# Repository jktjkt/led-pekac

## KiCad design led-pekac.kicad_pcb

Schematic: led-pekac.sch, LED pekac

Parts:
C1, C2: 10uF/50V; C_1206_3216Metric_Pad1.33x1.80mm_HandSolder
C3, C4: 22uF/10V; C_1206_3216Metric_Pad1.33x1.80mm_HandSolder
C5, C7: 1uF; C_1206_3216Metric_Pad1.33x1.80mm_HandSolder
C6: 47nF; C_1206_3216Metric_Pad1.33x1.80mm_HandSolder
C8, C9: 100nF; C_1206_3216Metric_Pad1.33x1.80mm_HandSolder
C10: 100nF; C_1210_3225Metric_Pad1.33x2.70mm_HandSolder
C11: 10uF Tantalum; CP_EIA-3528-21_Kemet-B_Pad1.50x2.35mm_HandSolder
D1: LED1; LED_1206_3216Metric_Castellated
D2: LED2; LED_1206_3216Metric_Castellated
D3: PWR; LED_1206_3216Metric_Castellated
J1: Conn_01x04; PinHeader_1x04_P2.54mm_Horizontal
J2: 24V; CUI_TB002-500-04BE
J3: Console; PinHeader_1x03_P2.54mm_Vertical
J4: Pi Zero; Raspberry_Pi_Zero_Socketed_THT_FaceDown_MountingHoles
J5: Cool; CUI_TB002-500-04BE
J6: Warm; CUI_TB002-500-04BE
J7: Conn_01x40_Female; SAMTEC_HLE-120-02-X-DV-PE-BE_no_internal_holes_reversed
Q1, Q2: 2N7002; SOT-23
Q3, Q4: IPD50N06S4L08ATMA2; TO-252-2
R1: 47k; R_1206_3216Metric_Pad1.30x1.75mm_HandSolder
R2, R3, R4, R5: 220k; R_1206_3216Metric_Pad1.30x1.75mm_HandSolder
R6, R7, R8: 160; R_1206_3216Metric_Pad1.30x1.75mm_HandSolder
R9, R10, R11, R12: 12.1k 0.1%; R_1206_3216Metric_Pad1.30x1.75mm_HandSolder
SW1: Wheel; Bourns-PEC12R-3220F-S0024-MFG
TP1: 5V; TestPoint_Loop_D3.50mm_Drill1.4mm_Beaded
TP2: 3.3V (Pi); TestPoint_Loop_D3.50mm_Drill1.4mm_Beaded
TP3: 3.3VA (LED); TestPoint_Loop_D3.50mm_Drill1.4mm_Beaded
TP4: SDA; TestPoint_Loop_D3.50mm_Drill1.4mm_Beaded
TP5: SCL; TestPoint_Loop_D3.50mm_Drill1.4mm_Beaded
TP6: GND; TestPoint_Loop_D3.50mm_Drill1.4mm_Beaded
TP7: PWM0; TestPoint_Loop_D3.50mm_Drill1.4mm_Beaded
TP8: PWM1; TestPoint_Loop_D3.50mm_Drill1.4mm_Beaded
U1: SWITCHING-3TERM-5V; CONV_P78E05-1000
U2: SWITCHING-3TERM-3V3; CONV_P78E05-1000
U3: MAX6956AAX+; MaximSSOP36
U4, U5: DA56-11GWA; DA56-11CGKWA
U6: TC1427COA; Microchip-TC1427COA-Level_A
U7: MCP3426A0-E/SN; SOIC-8_3.9x4.9mm_P1.27mm

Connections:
+3V3: C10.2, C11.1, J4.1 (3V3), J4.17 (3V3), J7.1, J7.17, R9.1, R10.1, R11.1, TP2.1, U7.3
+5V: C3.1, C7.1, C8.1, C9.1, J4.2 (5V), J4.4 (5V), J7.2, J7.4, R6.1, R7.1, R8.2, TP1.1, U1.3, U6.6
+24V: C1.1, C2.1, J2.1, J2.2, J5.3, J5.4, J6.1, J6.2, U1.1, U2.1
/Console_RX: J3.2, J4.10 (GPIO15/RXD), J7.10
/Console_TX: J3.3, J4.8 (GPIO14/TXD), J7.8
/Cool-: J5.1, J5.2, Q3.2
/NTC1_bias: J1.1, R10.2
/NTC1_sense: J1.2, U7.1
/NTC2_bias: J1.3, R9.2
/NTC2_sense: J1.4, U7.7
/PWM0: J4.32 (PWM0/GPIO12), J7.32, R3.1, TP7.1, U6.2
/PWM1: J4.33 (PWM1/GPIO13), J7.33, R2.1, TP8.1, U6.4
/Warm-: J6.3, J6.4, Q4.2
/adc_mid: R11.2, R12.1, U7.2, U7.8
/dig1_a: U3.21, U4.16
/dig1_b: U3.22, U4.15
/dig1_c: U3.16, U4.3
/dig1_d: U3.17, U4.2
/dig1_e: U3.18, U4.1
/dig1_f: U3.19, U4.18
/dig1_g: U3.20, U4.17
/dig2_a: U3.24, U4.11
/dig2_b: U3.25, U4.10
/dig2_c: U3.12, U4.8
/dig2_d: U3.14, U4.6
/dig2_e: U3.15, U4.5
/dig2_f: U3.23, U4.12
/dig2_g: U3.13, U4.7
/dig3_a: U3.28, U5.16
/dig3_b: U3.29, U5.15
/dig3_c: U3.9, U5.3
/dig3_d: U3.10, U5.2
/dig3_e: U3.11, U5.1
/dig3_f: U3.26, U5.18
/dig3_g: U3.27, U5.17
/dig4_a: U3.31, U5.11
/dig4_b: U3.32, U5.10
/dig4_c: U3.5, U5.8
/dig4_d: U3.7, U5.6
/dig4_e: U3.8, U5.5
/dig4_f: U3.30, U5.12
/dig4_g: U3.6, U5.7
/pi_07: J4.7 (GCLK0/GPIO4), J7.7
/pi_11: J4.11 (GPIO17), J7.11
/pi_12: J4.12 (GPIO18/PWM0), J7.12
/pi_13: J4.13 (GPIO27), J7.13
/pi_15: J4.15 (GPIO22), J7.15, SW1.A
/pi_16: J4.16 (GPIO23), J7.16, SW1.B
/pi_18: J4.18 (GPIO24), J7.18, SW1.1
/pi_19: J4.19 (MOSI0/GPIO10), J7.19
/pi_21: J4.21 (MISO0/GPIO9), J7.21
/pi_22: J4.22 (GPIO25), J7.22
/pi_23: J4.23 (SCLK0/GPIO11), J7.23
/pi_24: J4.24 (~CE0~/GPIO8), J7.24
/pi_26: J4.26 (~CE1~/GPIO7), J7.26
/pi_27: J4.27 (ID_SD/GPIO0), J7.27
/pi_28: J4.28 (ID_SC/GPIO1), J7.28
/pi_29: J4.29 (GCLK1/GPIO5), J7.29, Q1.1, R4.1
/pi_31: J4.31 (GCLK2/GPIO6), J7.31, Q2.1, R5.2
/pi_35: J4.35 (GPIO19/MISO1), J7.35
/pi_36: J4.36 (GPIO16), J7.36
/pi_37: J4.37 (GPIO26), J7.37
/pi_38: J4.38 (GPIO20/MOSI1), J7.38
/pi_40: J4.40 (GPIO21/SCLK1), J7.40
GND: C1.2, C2.2, C3.2, C4.2, C5.2, C6.1, C7.2, C8.2, C9.2, C10.1, C11.2, D3.1 (K), J2.3, J2.4, J3.1, J4.6 (GND), J4.9 (GND), J4.14 (GND), J4.20 (GND), J4.25 (GND), J4.30 (GND), J4.34 (GND), J4.39 (GND), J7.6, J7.9, J7.14, J7.20, J7.25, J7.30, J7.34, J7.39, Q1.2, Q2.2, Q3.3, Q4.3, R1.2, R2.2, R3.2, R4.2, R5.1, R12.2, SW1.2, SW1.C, TP6.1, U1.2, U2.2, U3.2, U3.3, U3.4, U3.35, U6.3, U7.6
I2C_SCL: J4.5 (SCL/GPIO3), J7.5, TP5.1, U3.34, U7.5
I2C_SDA: J4.3 (SDA/GPIO2), J7.3, TP4.1, U3.33, U7.4
unnamed: D1.1 (K), Q1.3
unnamed: D1.2 (A), R6.2
unnamed: D2.1 (K), Q2.3
unnamed: D2.2 (A), R7.2
unnamed: D3.2 (A), R8.1
unnamed: Q3.1, U6.7
unnamed: Q4.1, U6.5
unnamed: R1.1, U3.1

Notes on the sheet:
Addr: 0x40

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
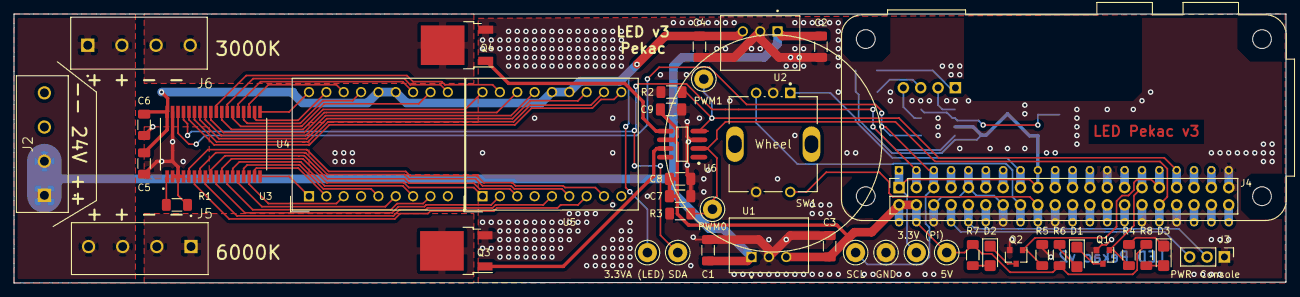
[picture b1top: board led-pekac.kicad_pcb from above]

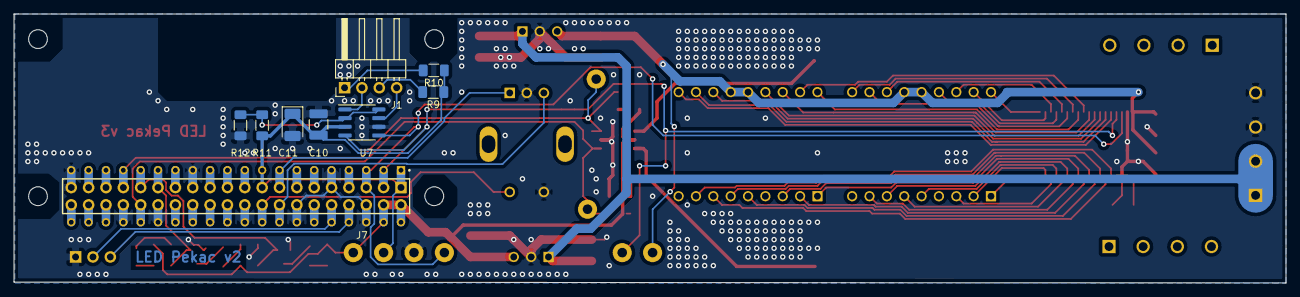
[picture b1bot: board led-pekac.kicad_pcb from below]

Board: 2 copper layers, 186.2 x 39.4 mm, 53 parts (9 on the bottom side), 76 nets.

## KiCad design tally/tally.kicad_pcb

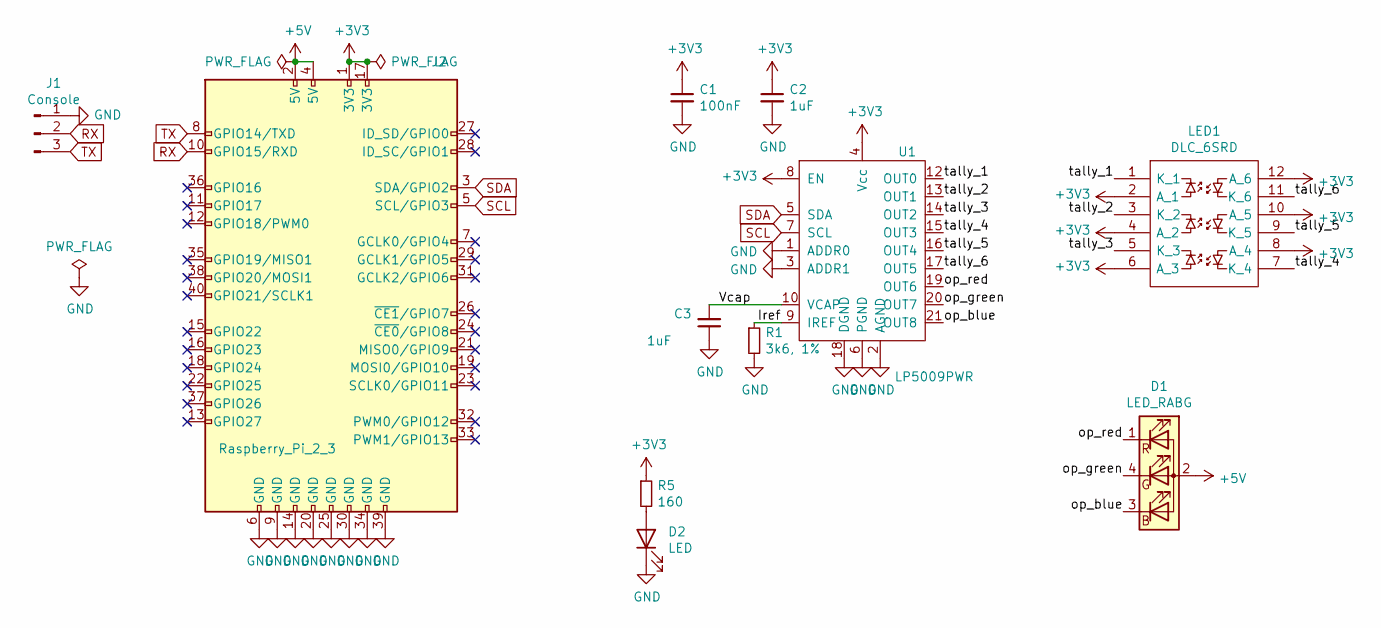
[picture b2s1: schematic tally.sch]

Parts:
C1: 100nF; C_1206_3216Metric_Pad1.33x1.80mm_HandSolder
C2, C3: 1uF; C_1206_3216Metric_Pad1.33x1.80mm_HandSolder
D1: LED_RABG; LED_D5.0mm-4_RGB
D2: LED; LED_1206_3216Metric_Castellated
J1: Console; PinHeader_1x03_P2.54mm_Horizontal
J2: Raspberry_Pi_2_3; Raspberry_Pi_Zero_Socketed_THT_FaceDown_MountingHolesExclus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
LED1: DLC_6SRD; DLC6SRD; Manufacturer_Part_Number DLC/6SRD; Mouser Part Number 604-DLC6SRD
R1: 3k6, 1%; R_1206_3216Metric_Pad1.30x1.75mm_HandSolder
R5: 160; R_1206_3216Metric_Pad1.30x1.75mm_HandSolder
U1: LP5009PWR; TSSOP-24_4.4x7.8mm_P0.65mm

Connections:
+3V3: C1.1, C2.1, J2.1 (3V3), J2.17 (3V3), LED1.2 (A_1), LED1.4 (A_2), LED1.6 (A_3), LED1.8 (A_4), LED1.10 (A_5), LED1.12 (A_6), R5.1, U1.4 (Vcc), U1.8 (EN)
+5V: D1.2 (A), J2.2 (5V), J2.4 (5V)
/Iref: R1.1, U1.9 (IREF)
/Vcap: C3.2, U1.10 (VCAP)
/op_blue: D1.3 (BK), U1.21 (OUT8)
/op_green: D1.4 (GK), U1.20 (OUT7)
/op_red: D1.1 (RK), U1.19 (OUT6)
/tally_1: LED1.1 (K_1), U1.12 (OUT0)
/tally_2: LED1.3 (K_2), U1.13 (OUT1)
/tally_3: LED1.5 (K_3), U1.14 (OUT2)
/tally_4: LED1.7 (K_4), U1.15 (OUT3)
/tally_5: LED1.9 (K_5), U1.16 (OUT4)
/tally_6: LED1.11 (K_6), U1.17 (OUT5)
GND: C1.2, C2.2, C3.1, D2.1 (K), J1.1, J2.6 (GND), J2.9 (GND), J2.14 (GND), J2.20 (GND), J2.25 (GND), J2.30 (GND), J2.34 (GND), J2.39 (GND), R1.2, U1.1 (ADDR0), U1.2 (AGND), U1.3 (ADDR1), U1.6 (PGND), U1.18 (DGND)
unnamed: D2.2 (A), R5.2
RX: J1.2, J2.10 (GPIO15/RXD)
SCL: J2.5 (SCL/GPIO3), U1.7 (SCL)
SDA: J2.3 (SDA/GPIO2), U1.5 (SDA)
TX: J1.3, J2.8 (GPIO14/TXD)

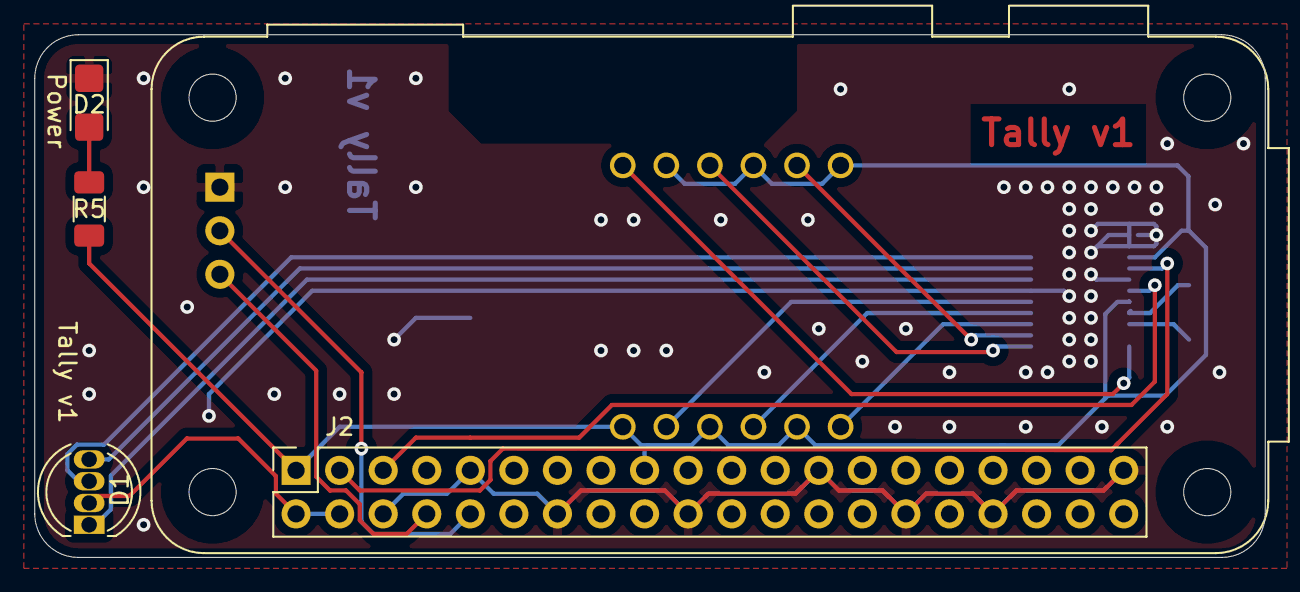
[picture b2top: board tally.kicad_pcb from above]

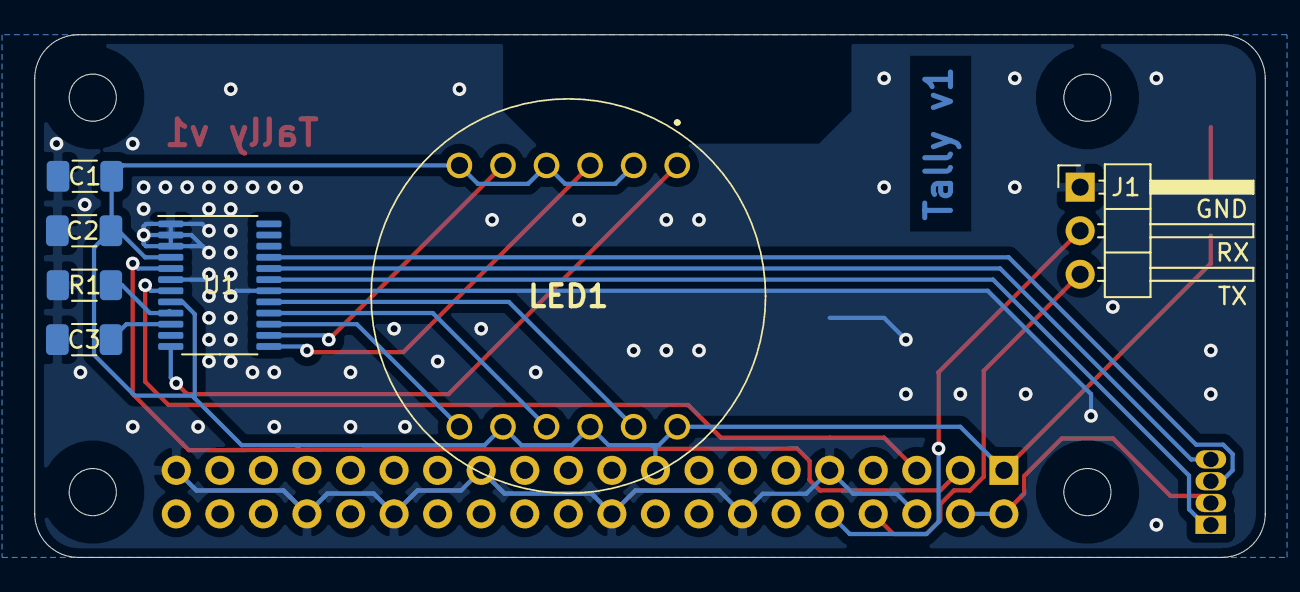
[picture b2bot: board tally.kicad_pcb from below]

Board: 2 copper layers, 71.8 x 30.5 mm, 11 parts (7 on the bottom side), 19 nets.

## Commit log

2021-06-30 Trying to create a component for MAX6596AAX+
2021-07-13 Let's see if this PCB works
2021-07-13 Add exported PDFs
2021-07-14 update component values
2021-07-17 fix the 3D model
2021-07-17 Fix two serious routing bugs
    The `dig4_c` trace was, unfortunately, left unconnected after my night
    pour optimization (...). I had to add a fixup wire to the first
    prototype.
    Also, the Pi module's footprint is a bit larger than the silkscreen
    because the SD card protrudes a little bit to the left, towards the
    rotary encoder. I tried to make this less urgent (note that I'm
2021-07-19 Show the current parameter on display
2021-07-28 wrk?
2021-07-28 PCB and schematics for the Tally light
2021-08-08 FW image for the tally light
2021-08-08 White preview LED indicates the tally thingy starting up
    In my testing it stays lit for about five seconds on Pi Zero W. That's
    plenty of time to notice, and a useful indication for each device
    restart I suppose.
2021-08-08 Make sure USB OTG is powered up
    Sometimes I've seen this thing stuck, with no entries but the root hub
    appearing in `lsusb`. This register seems to do the trick.
    Tested with 5Dii which was the camera that first showed these symptoms.
2023-06-17 tally: control via MQTT
2023-06-17 forgotten update
2023-06-17 some long-fogotten buildroot config
2023-06-17 tally light: export PDFs
2023-06-17 I think this is what runs on the devices
    Oh the joy of commiting nsome two-year-old, last-minute patches, yay.
